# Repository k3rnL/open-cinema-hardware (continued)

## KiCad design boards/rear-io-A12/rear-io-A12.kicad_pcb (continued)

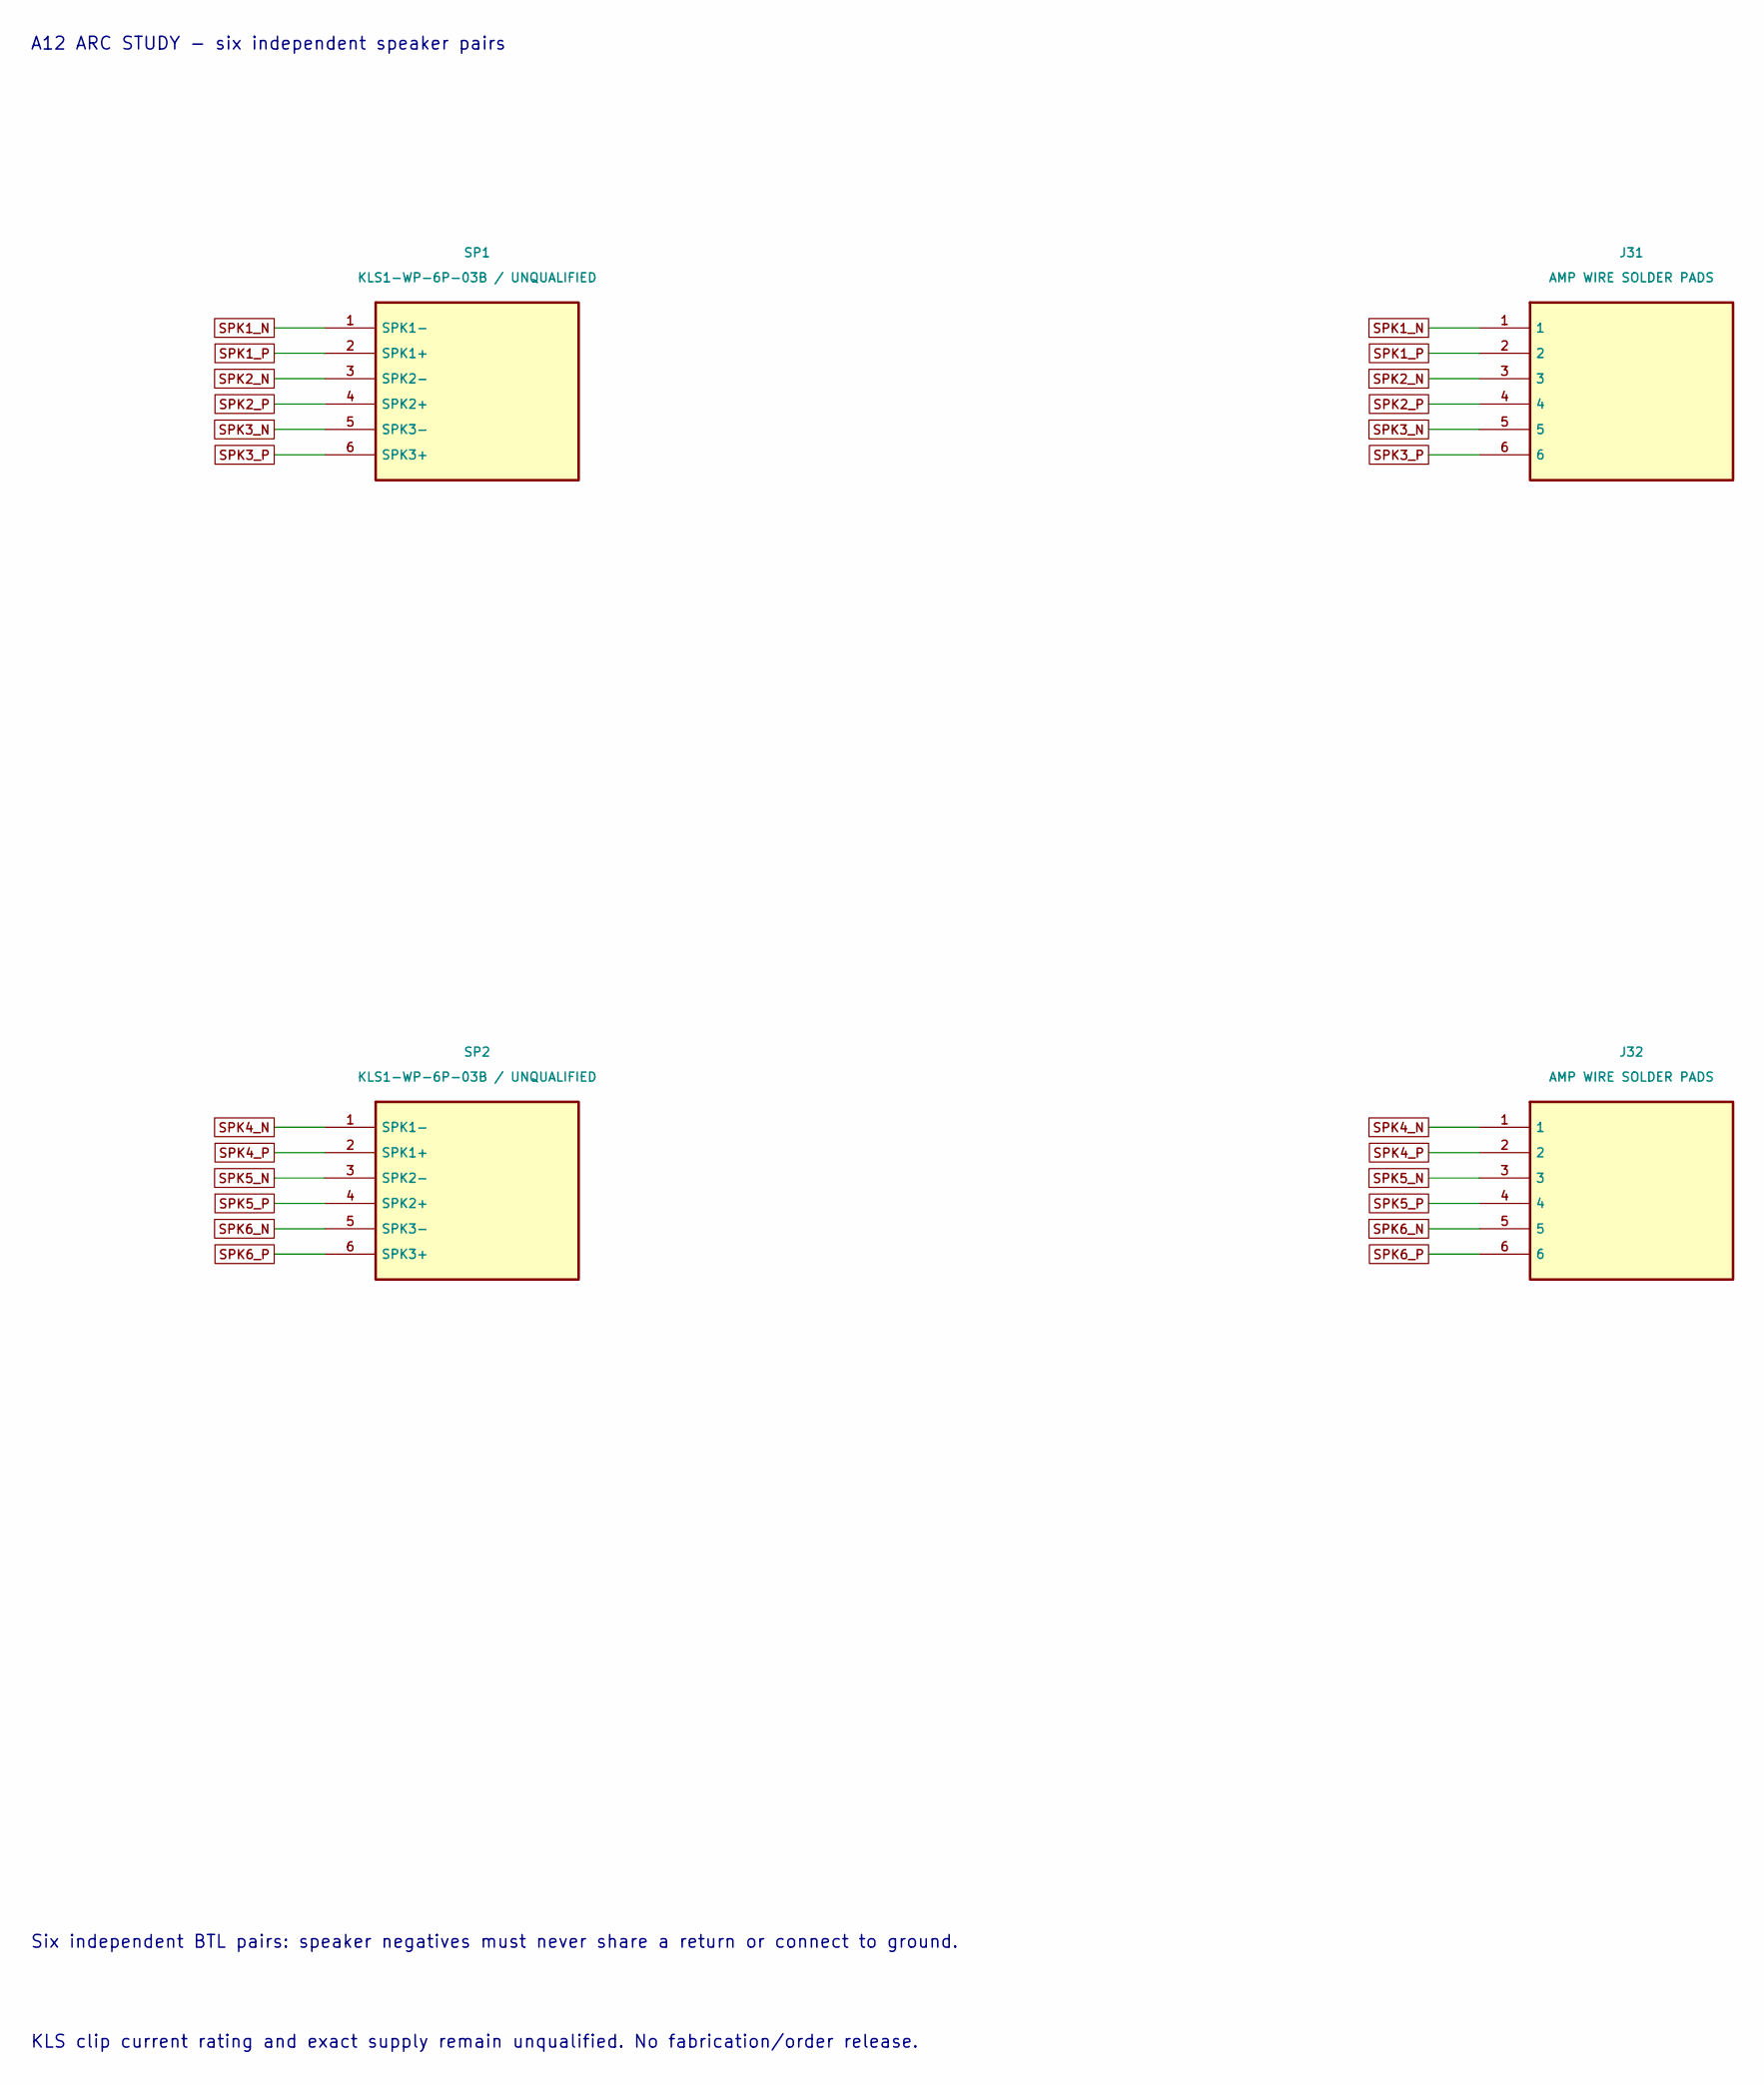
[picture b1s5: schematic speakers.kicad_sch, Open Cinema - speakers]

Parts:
J31, J32: AMP WIRE SOLDER PADS; SolderWire-1sqmm_1x06_P5.4mm_D1.4mm_OD2.7mm; MPN PCB_SOLDER_PADS_1SQMM
SP1, SP2: KLS1-WP-6P-03B / UNQUALIFIED; KLS1_WP_6P_03B_Horizontal_A8; MPN L-KLS1-WP-6P-03B-B/R

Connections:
SPK1_N: J31.1, SP1.1 (SPK1-)
SPK1_P: J31.2, SP1.2 (SPK1+)
SPK2_N: J31.3, SP1.3 (SPK2-)
SPK2_P: J31.4, SP1.4 (SPK2+)
SPK3_N: J31.5, SP1.5 (SPK3-)
SPK3_P: J31.6, SP1.6 (SPK3+)
SPK4_N: J32.1, SP2.1 (SPK1-)
SPK4_P: J32.2, SP2.2 (SPK1+)
SPK5_N: J32.3, SP2.3 (SPK2-)
SPK5_P: J32.4, SP2.4 (SPK2+)
SPK6_N: J32.5, SP2.5 (SPK3-)
SPK6_P: J32.6, SP2.6 (SPK3+)

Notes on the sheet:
A12 ARC STUDY - six independent speaker pairs
Six independent BTL pairs: speaker negatives must never share a return or connect to ground.
KLS clip current rating and exact supply remain unqualified. No fabrication/order release.

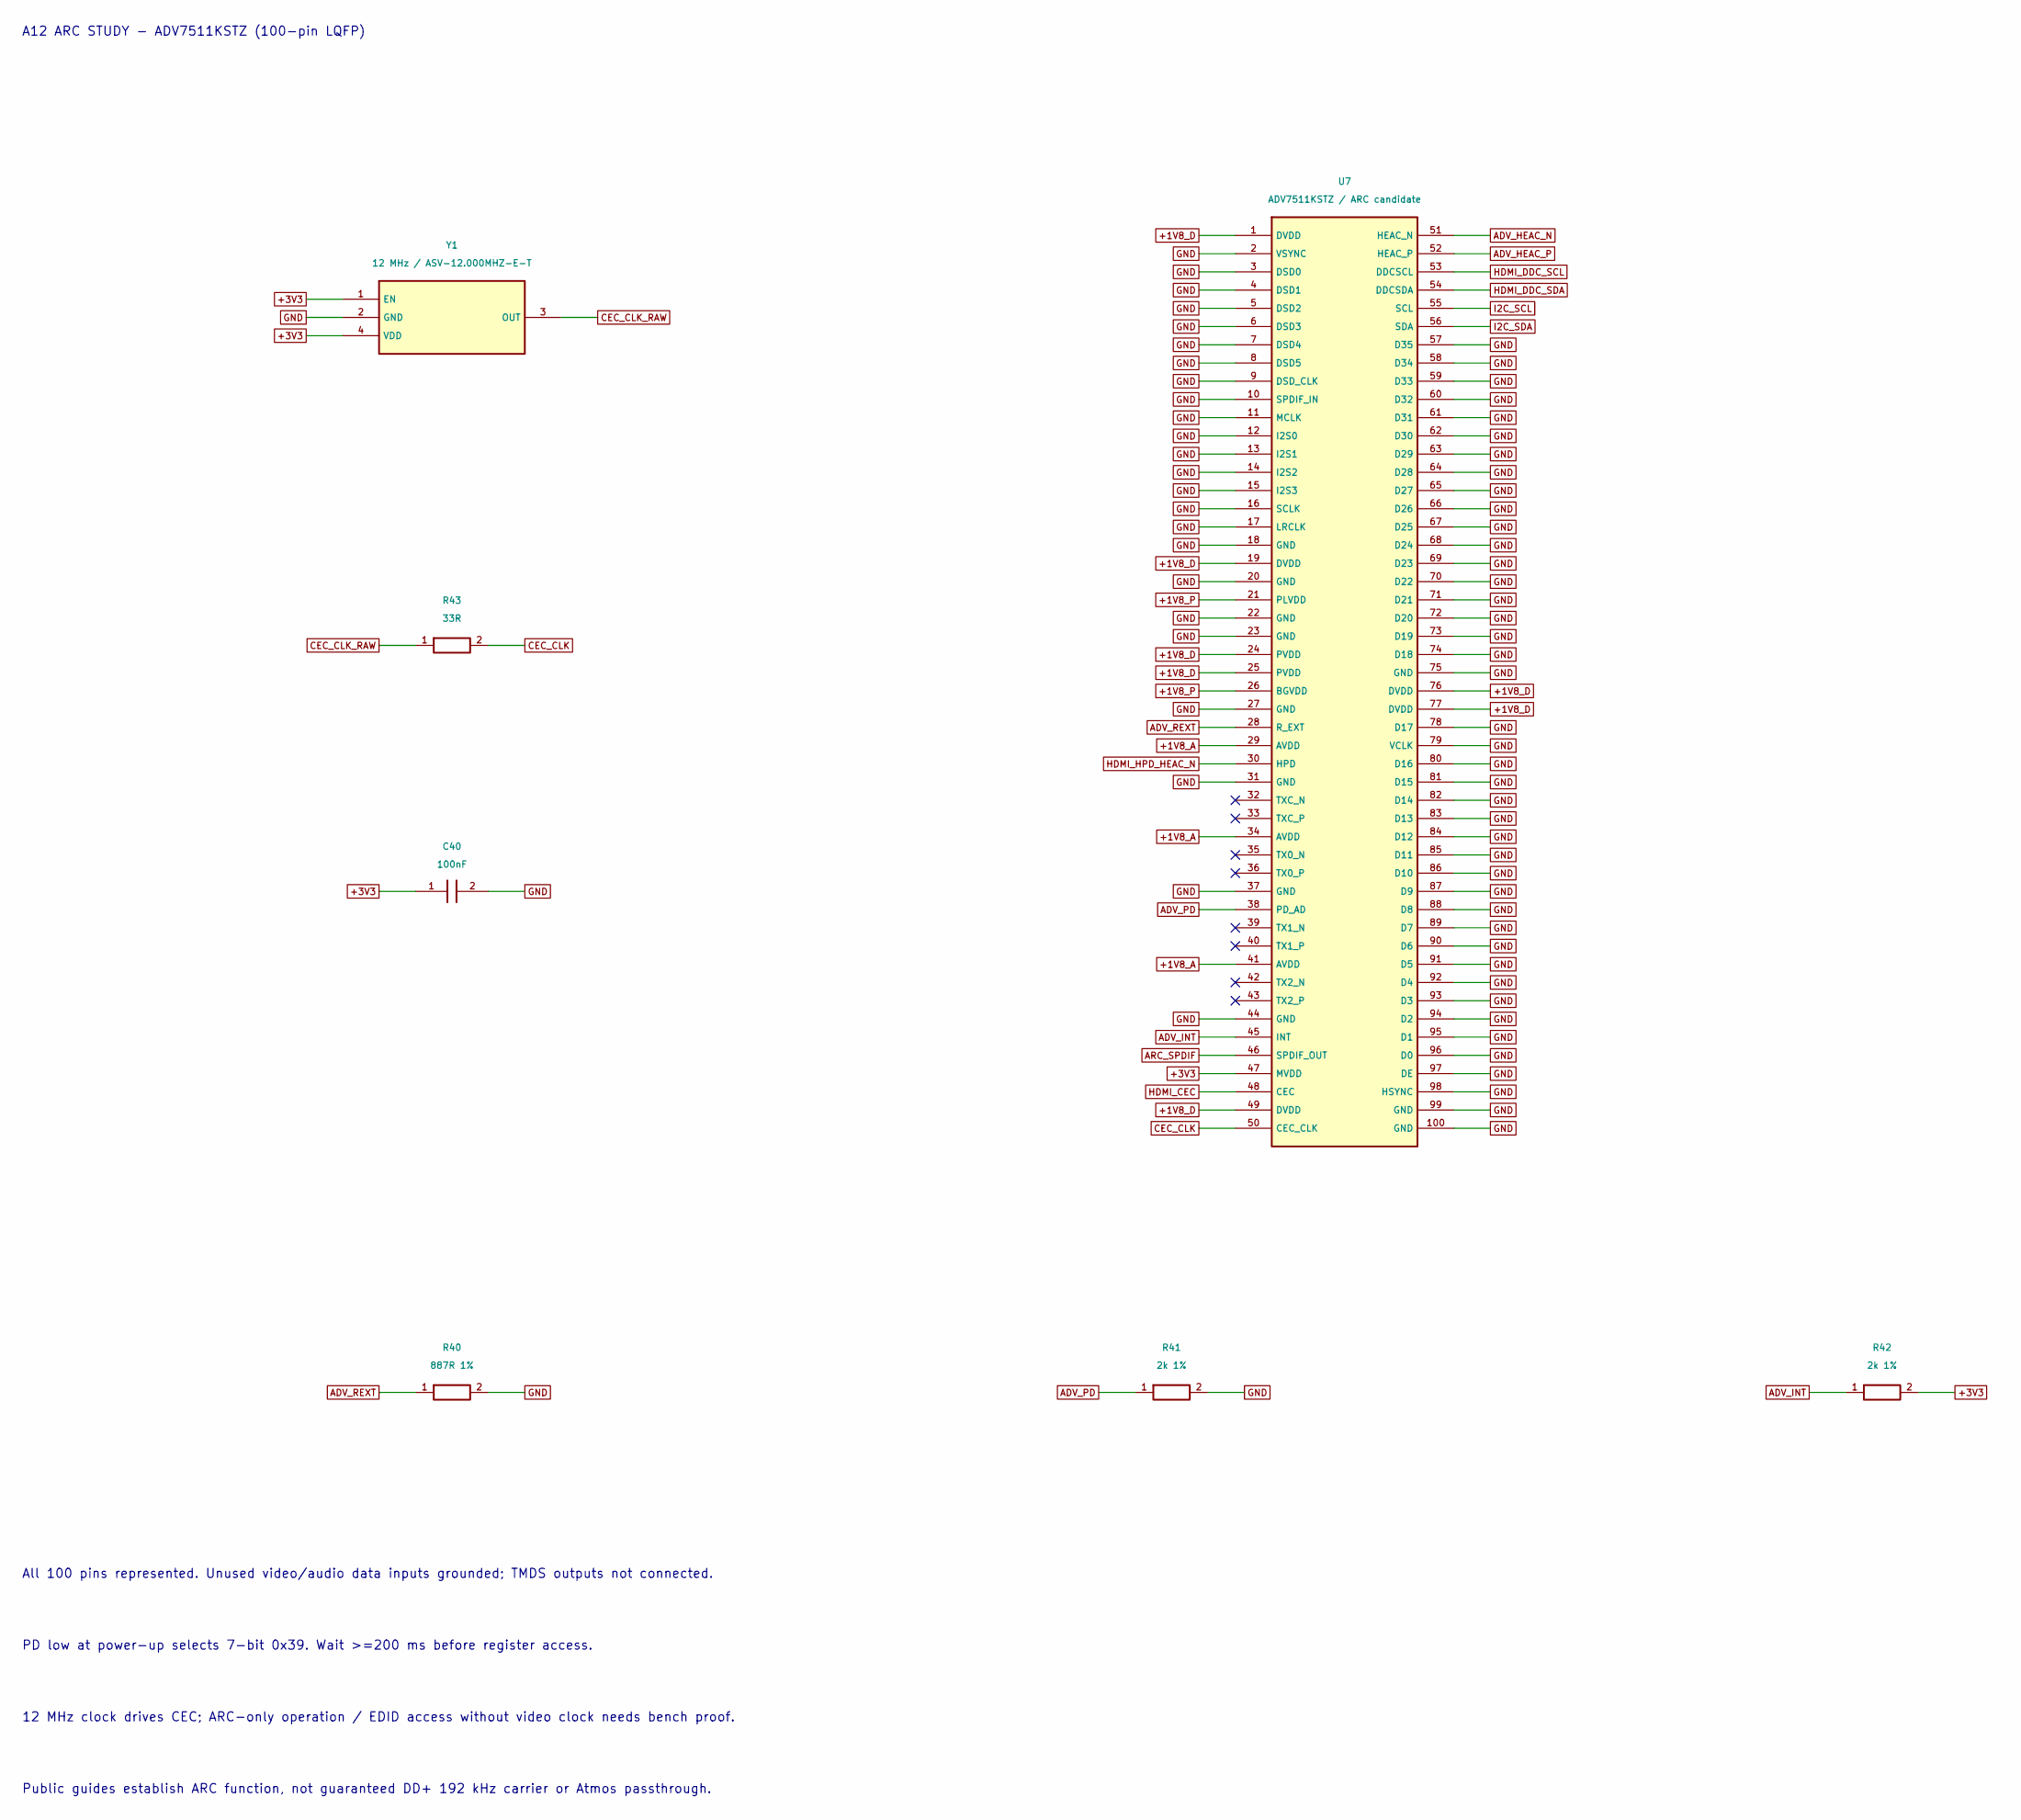
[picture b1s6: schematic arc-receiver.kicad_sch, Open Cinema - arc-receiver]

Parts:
C40: 100nF; C_0603_1608Metric; MPN CL10B104KB8NNNC
R40: 887R 1%; R_0603_1608Metric; MPN RC0603FR-07887RL
R41, R42: 2k 1%; R_0603_1608Metric; MPN RC0603FR-072KL
R43: 33R; R_0603_1608Metric; MPN RC0603FR-0733RL
U7: ADV7511KSTZ / ARC candidate; LQFP-100_14x14mm_P0.5mm; MPN ADV7511KSTZ
Y1: 12 MHz / ASV-12.000MHZ-E-T; Oscillator_SMD_Abracon_ASV-4Pin_7.0x5.1mm; MPN ASV-12.000MHZ-E-T

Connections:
+1V8_A: U7.29 (AVDD), U7.34 (AVDD), U7.41 (AVDD); also elsewhere on the board
+1V8_D: U7.1 (DVDD), U7.19 (DVDD), U7.24 (PVDD), U7.25 (PVDD), U7.49 (DVDD), U7.76 (DVDD), U7.77 (DVDD); also elsewhere on the board
+1V8_P: U7.21 (PLVDD), U7.26 (BGVDD); also elsewhere on the board
+3V3: C40.1, R42.2, U7.47 (MVDD), Y1.1 (EN), Y1.4 (VDD); also elsewhere on the board
ADV_HEAC_N: U7.51 (HEAC_N); also elsewhere on the board
ADV_HEAC_P: U7.52 (HEAC_P); also elsewhere on the board
ADV_INT: R42.1, U7.45 (INT); also elsewhere on the board
ADV_PD: R41.1, U7.38 (PD_AD)
ADV_REXT: R40.1, U7.28 (R_EXT)
ARC_SPDIF: U7.46 (SPDIF_OUT); also elsewhere on the board
CEC_CLK: R43.2, U7.50 (CEC_CLK)
CEC_CLK_RAW: R43.1, Y1.3 (OUT)
GND: C40.2, R40.2, R41.2, U7.2 (VSYNC), U7.3 (DSD0), U7.4 (DSD1), U7.5 (DSD2), U7.6 (DSD3), U7.7 (DSD4), U7.8 (DSD5), U7.9 (DSD_CLK), U7.10 (SPDIF_IN), U7.11 (MCLK), U7.12 (I2S0), U7.13 (I2S1), U7.14 (I2S2), U7.15 (I2S3), U7.16 (SCLK), U7.17 (LRCLK), U7.18 (GND), U7.20 (GND), U7.22 (GND), U7.23 (GND), U7.27 (GND), U7.31 (GND), U7.37 (GND), U7.44 (GND), U7.57 (D35), U7.58 (D34), U7.59 (D33), U7.60 (D32), U7.61 (D31), U7.62 (D30), U7.63 (D29), U7.64 (D28), U7.65 (D27), U7.66 (D26), U7.67 (D25), U7.68 (D24), U7.69 (D23), U7.70 (D22), U7.71 (D21), U7.72 (D20), U7.73 (D19), U7.74 (D18), U7.75 (GND), U7.78 (D17), U7.79 (VCLK), U7.80 (D16), U7.81 (D15), U7.82 (D14), U7.83 (D13), U7.84 (D12), U7.85 (D11), U7.86 (D10), U7.87 (D9), U7.88 (D8), U7.89 (D7), U7.90 (D6), U7.91 (D5), U7.92 (D4), U7.93 (D3), U7.94 (D2), U7.95 (D1), U7.96 (D0), U7.97 (DE), U7.98 (HSYNC), U7.99 (GND), U7.100 (GND), Y1.2 (GND); also elsewhere on the board
HDMI_CEC: U7.48 (CEC); also elsewhere on the board
HDMI_DDC_SCL: U7.53 (DDCSCL); also elsewhere on the board
HDMI_DDC_SDA: U7.54 (DDCSDA); also elsewhere on the board
HDMI_HPD_HEAC_N: U7.30 (HPD); also elsewhere on the board
I2C_SCL: U7.55 (SCL); also elsewhere on the board
I2C_SDA: U7.56 (SDA); also elsewhere on the board

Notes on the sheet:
A12 ARC STUDY - ADV7511KSTZ (100-pin LQFP)
All 100 pins represented. Unused video/audio data inputs grounded; TMDS outputs not connected.
PD low at power-up selects 7-bit 0x39. Wait >=200 ms before register access.
12 MHz clock drives CEC; ARC-only operation / EDID access without video clock needs bench proof.
Public guides establish ARC function, not guaranteed DD+ 192 kHz carrier or Atmos passthrough.

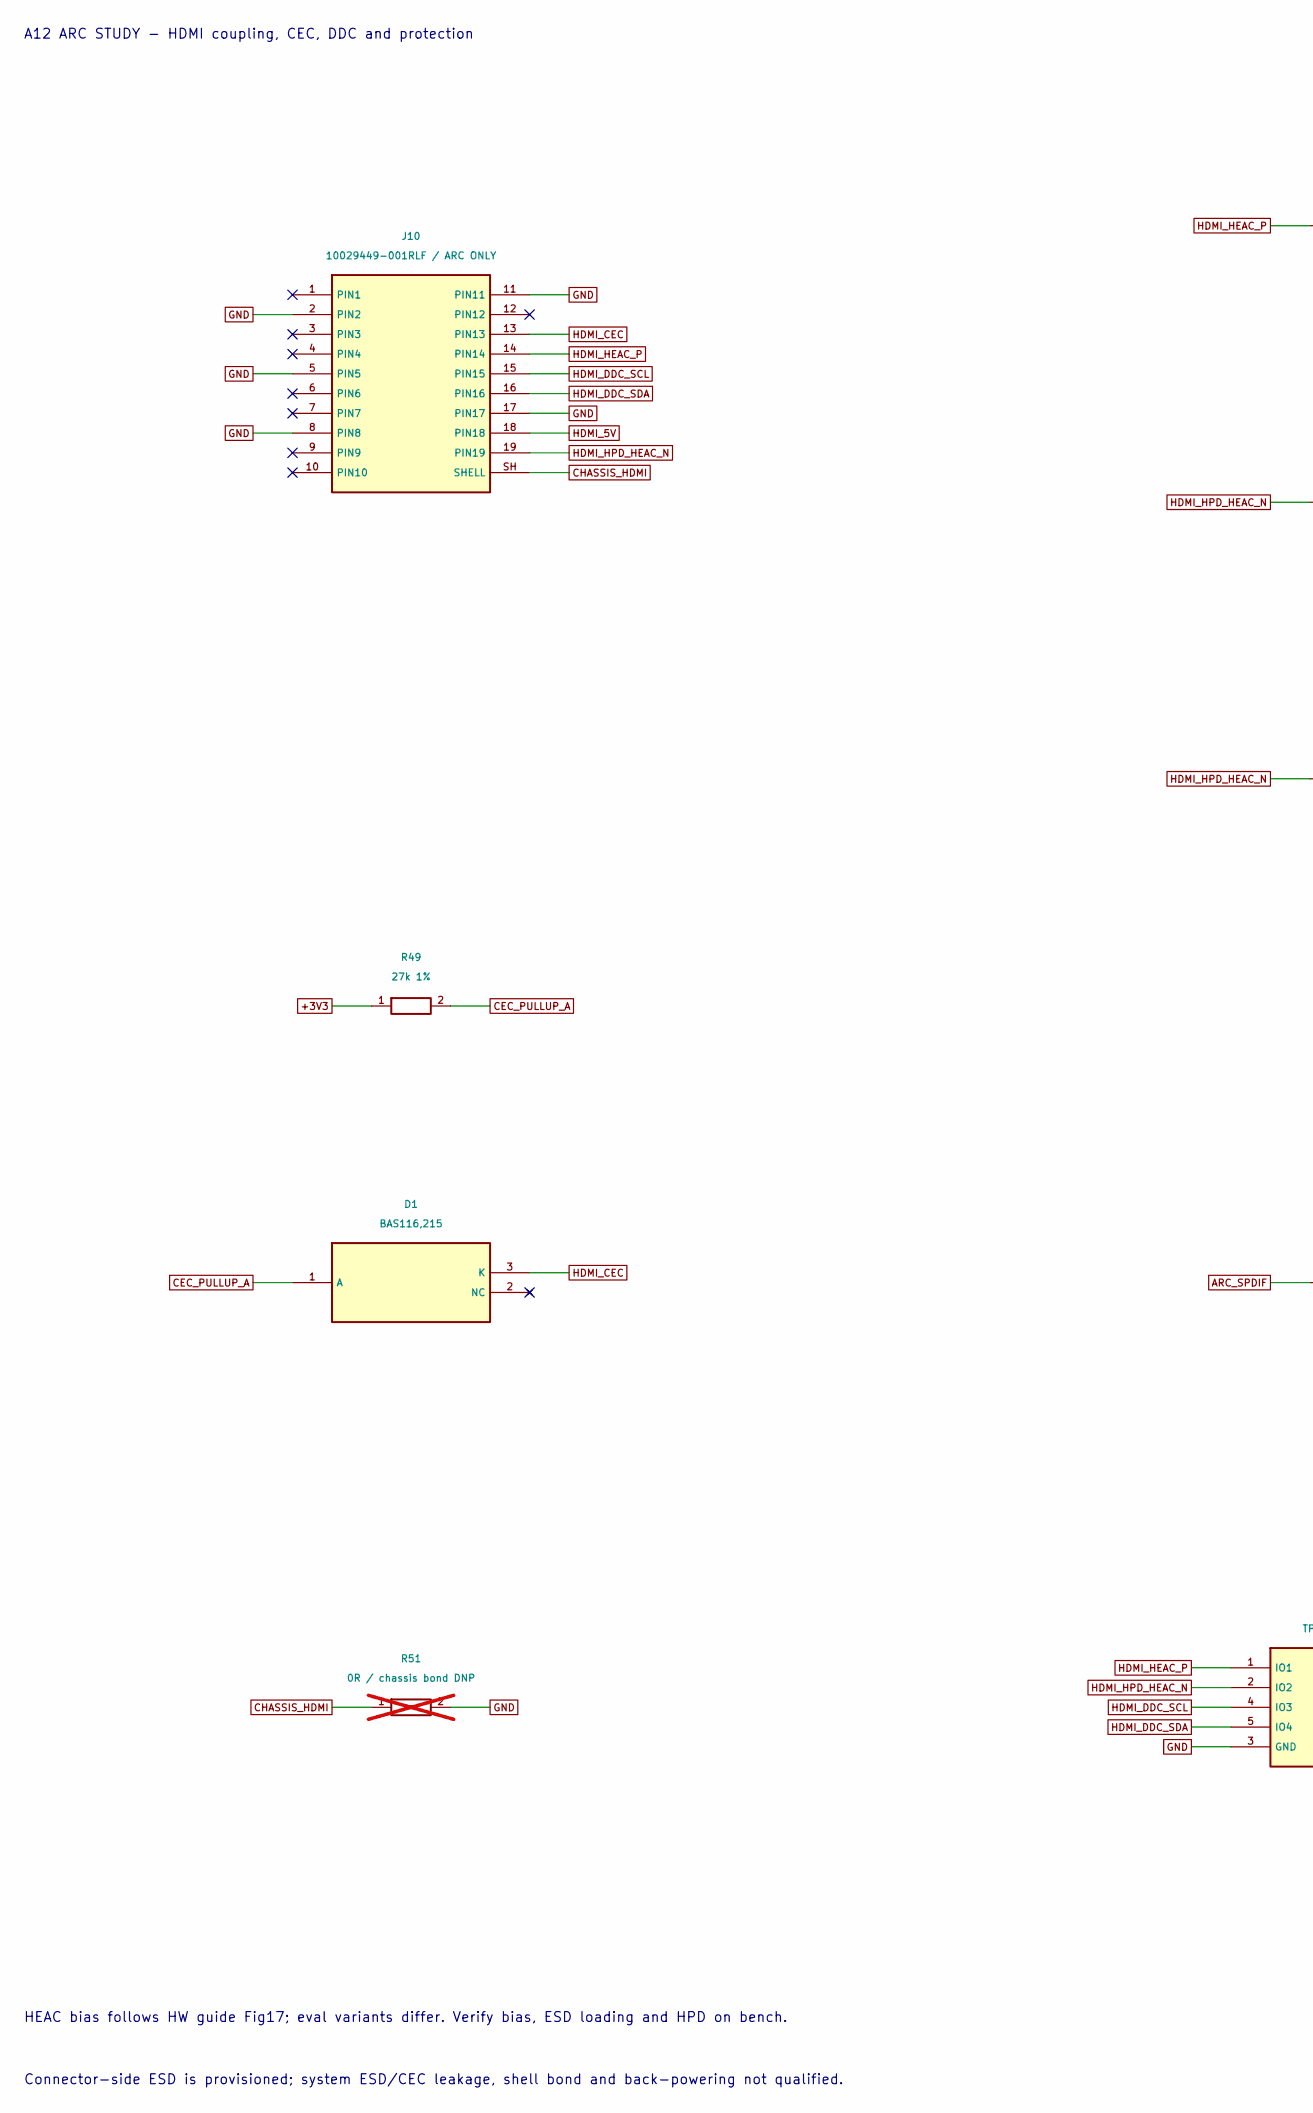
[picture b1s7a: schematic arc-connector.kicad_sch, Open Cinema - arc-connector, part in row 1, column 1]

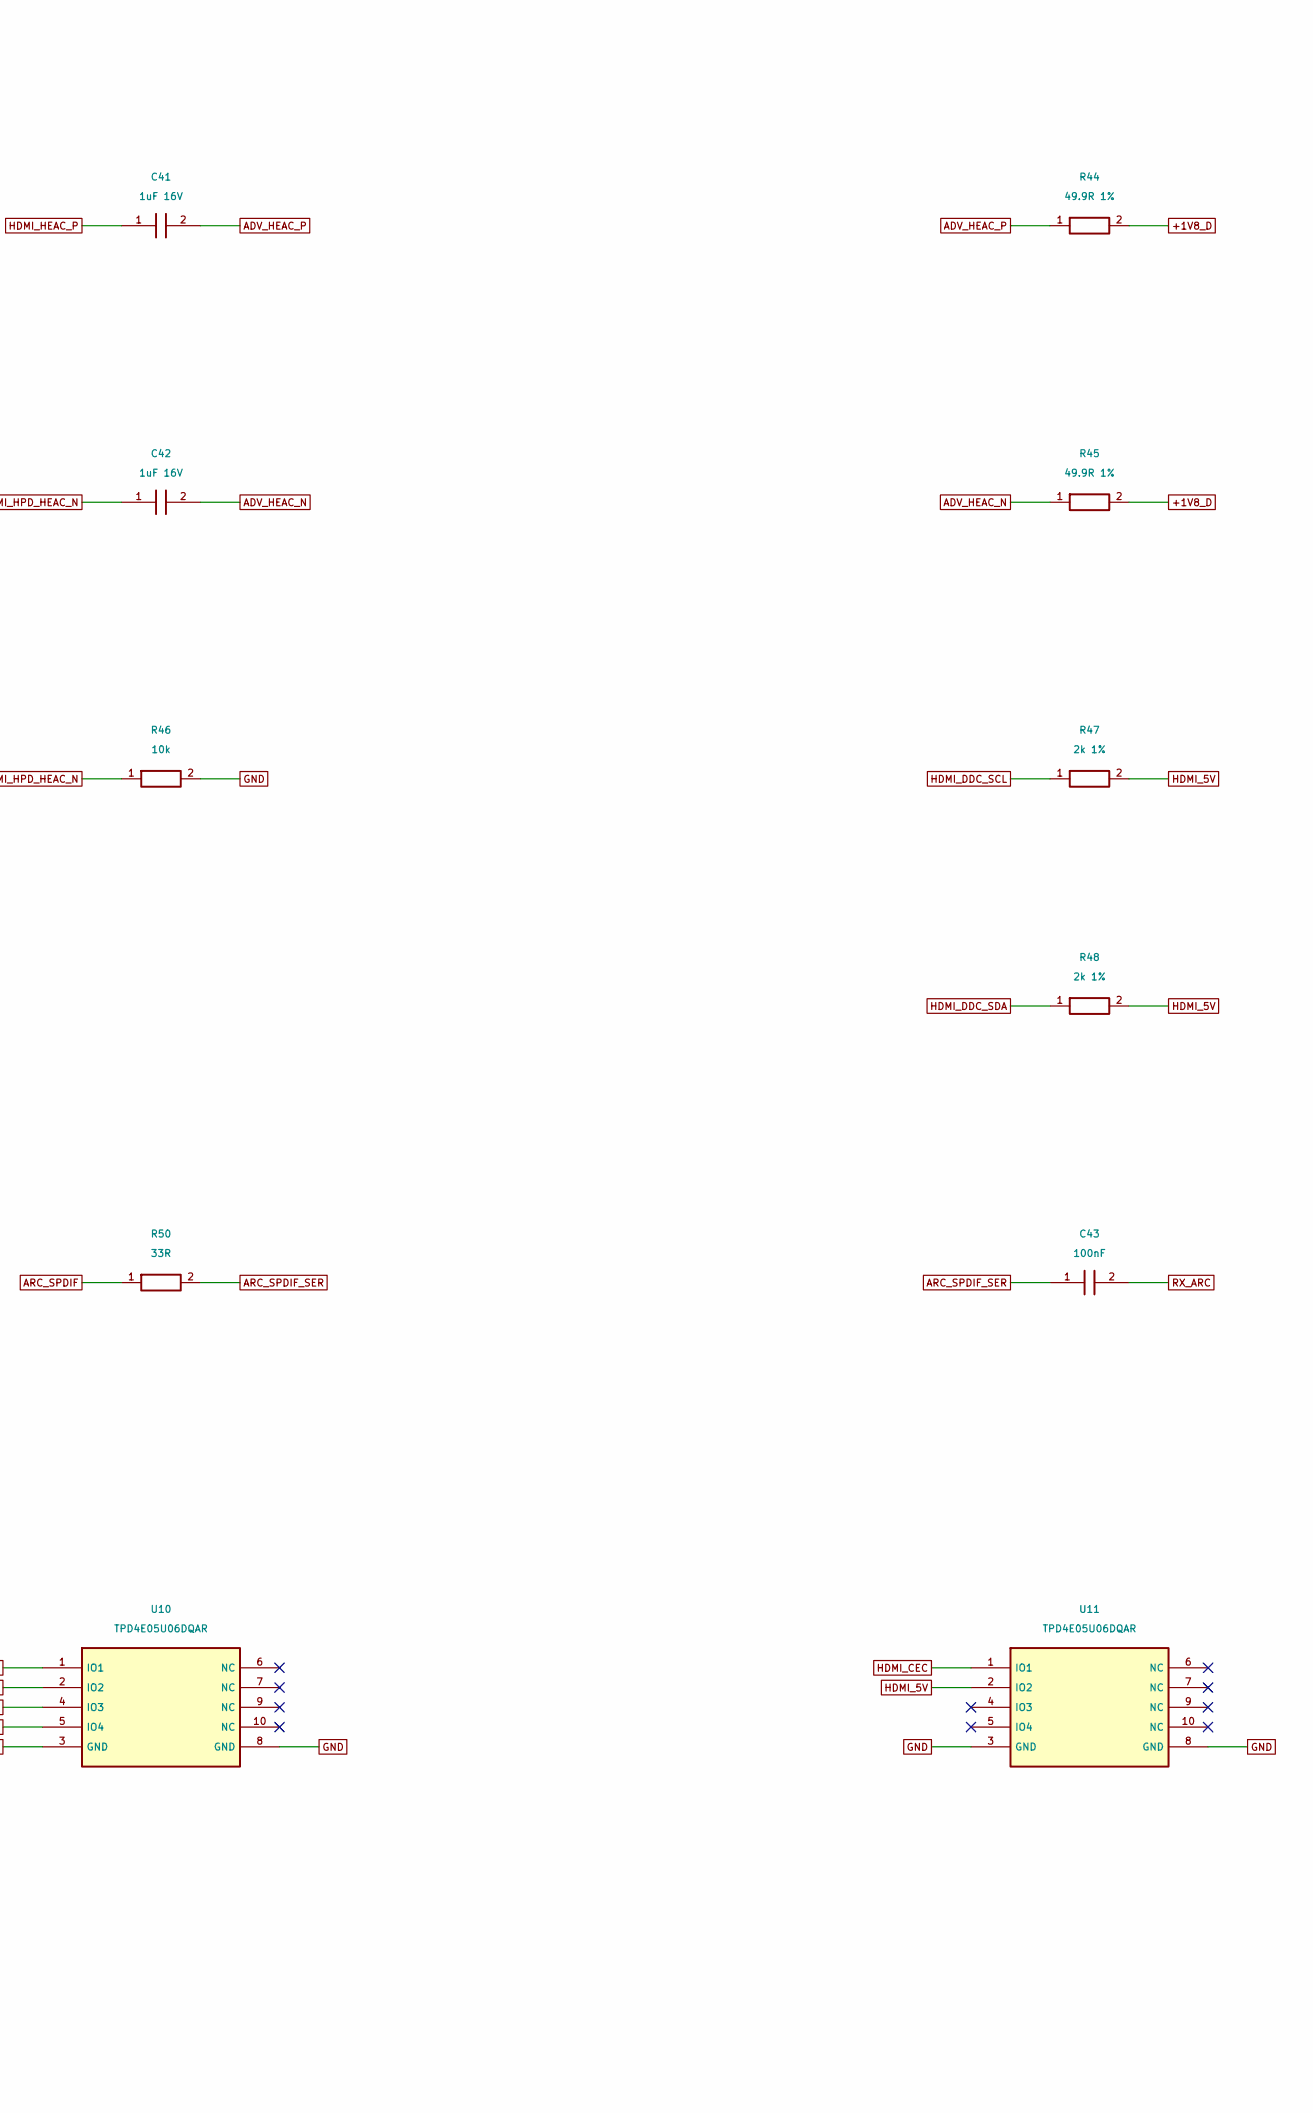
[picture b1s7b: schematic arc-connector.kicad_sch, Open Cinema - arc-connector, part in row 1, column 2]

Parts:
C41, C42: 1uF 16V; C_0603_1608Metric; MPN CL10B105KO8NNNC
C43: 100nF; C_0603_1608Metric; MPN CL10B104KB8NNNC
D1: BAS116,215; SOT-23; MPN BAS116,215
J10: 10029449-001RLF / ARC ONLY; HDMI_A_Amphenol_10029449-x01xLF_Horizontal; MPN 10029449-001RLF
R44, R45: 49.9R 1%; R_0603_1608Metric; MPN RC0603FR-0749R9L
R46: 10k; R_0603_1608Metric; MPN RC0603FR-0710KL
R47, R48: 2k 1%; R_0603_1608Metric; MPN RC0603FR-072KL
R49: 27k 1%; R_0603_1608Metric; MPN RC0603FR-0727KL
R50: 33R; R_0603_1608Metric; MPN RC0603FR-0733RL
R51: 0R / chassis bond DNP; R_0603_1608Metric; MPN RC0603JR-070RL; not fitted
U10, U11: TPD4E05U06DQAR; USON-10_2.5x1.0mm_P0.5mm; MPN TPD4E05U06DQAR

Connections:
+1V8_D: R44.2, R45.2; also elsewhere on the board
+3V3: R49.1; also elsewhere on the board
ADV_HEAC_N: C42.2, R45.1; also elsewhere on the board
ADV_HEAC_P: C41.2, R44.1; also elsewhere on the board
ARC_SPDIF: R50.1; also elsewhere on the board
ARC_SPDIF_SER: C43.1, R50.2
CEC_PULLUP_A: D1.1 (A), R49.2
CHASSIS_HDMI: J10.SH (SHELL), R51.1
GND: J10.2 (PIN2), J10.5 (PIN5), J10.8 (PIN8), J10.11 (PIN11), J10.17 (PIN17), R46.2, R51.2, U10.3 (GND), U10.8 (GND), U11.3 (GND), U11.8 (GND); also elsewhere on the board
HDMI_5V: J10.18 (PIN18), R47.2, R48.2, U11.2 (IO2); also elsewhere on the board
HDMI_CEC: D1.3 (K), J10.13 (PIN13), U11.1 (IO1); also elsewhere on the board
HDMI_DDC_SCL: J10.15 (PIN15), R47.1, U10.4 (IO3); also elsewhere on the board
HDMI_DDC_SDA: J10.16 (PIN16), R48.1, U10.5 (IO4); also elsewhere on the board
HDMI_HEAC_P: C41.1, J10.14 (PIN14), U10.1 (IO1)
HDMI_HPD_HEAC_N: C42.1, J10.19 (PIN19), R46.1, U10.2 (IO2); also elsewhere on the board
RX_ARC: C43.2; also elsewhere on the board

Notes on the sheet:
A12 ARC STUDY - HDMI coupling, CEC, DDC and protection
HEAC bias follows HW guide Fig17; eval variants differ. Verify bias, ESD loading and HPD on bench.
Connector-side ESD is provisioned; system ESD/CEC leakage, shell bond and back-powering not qualified.

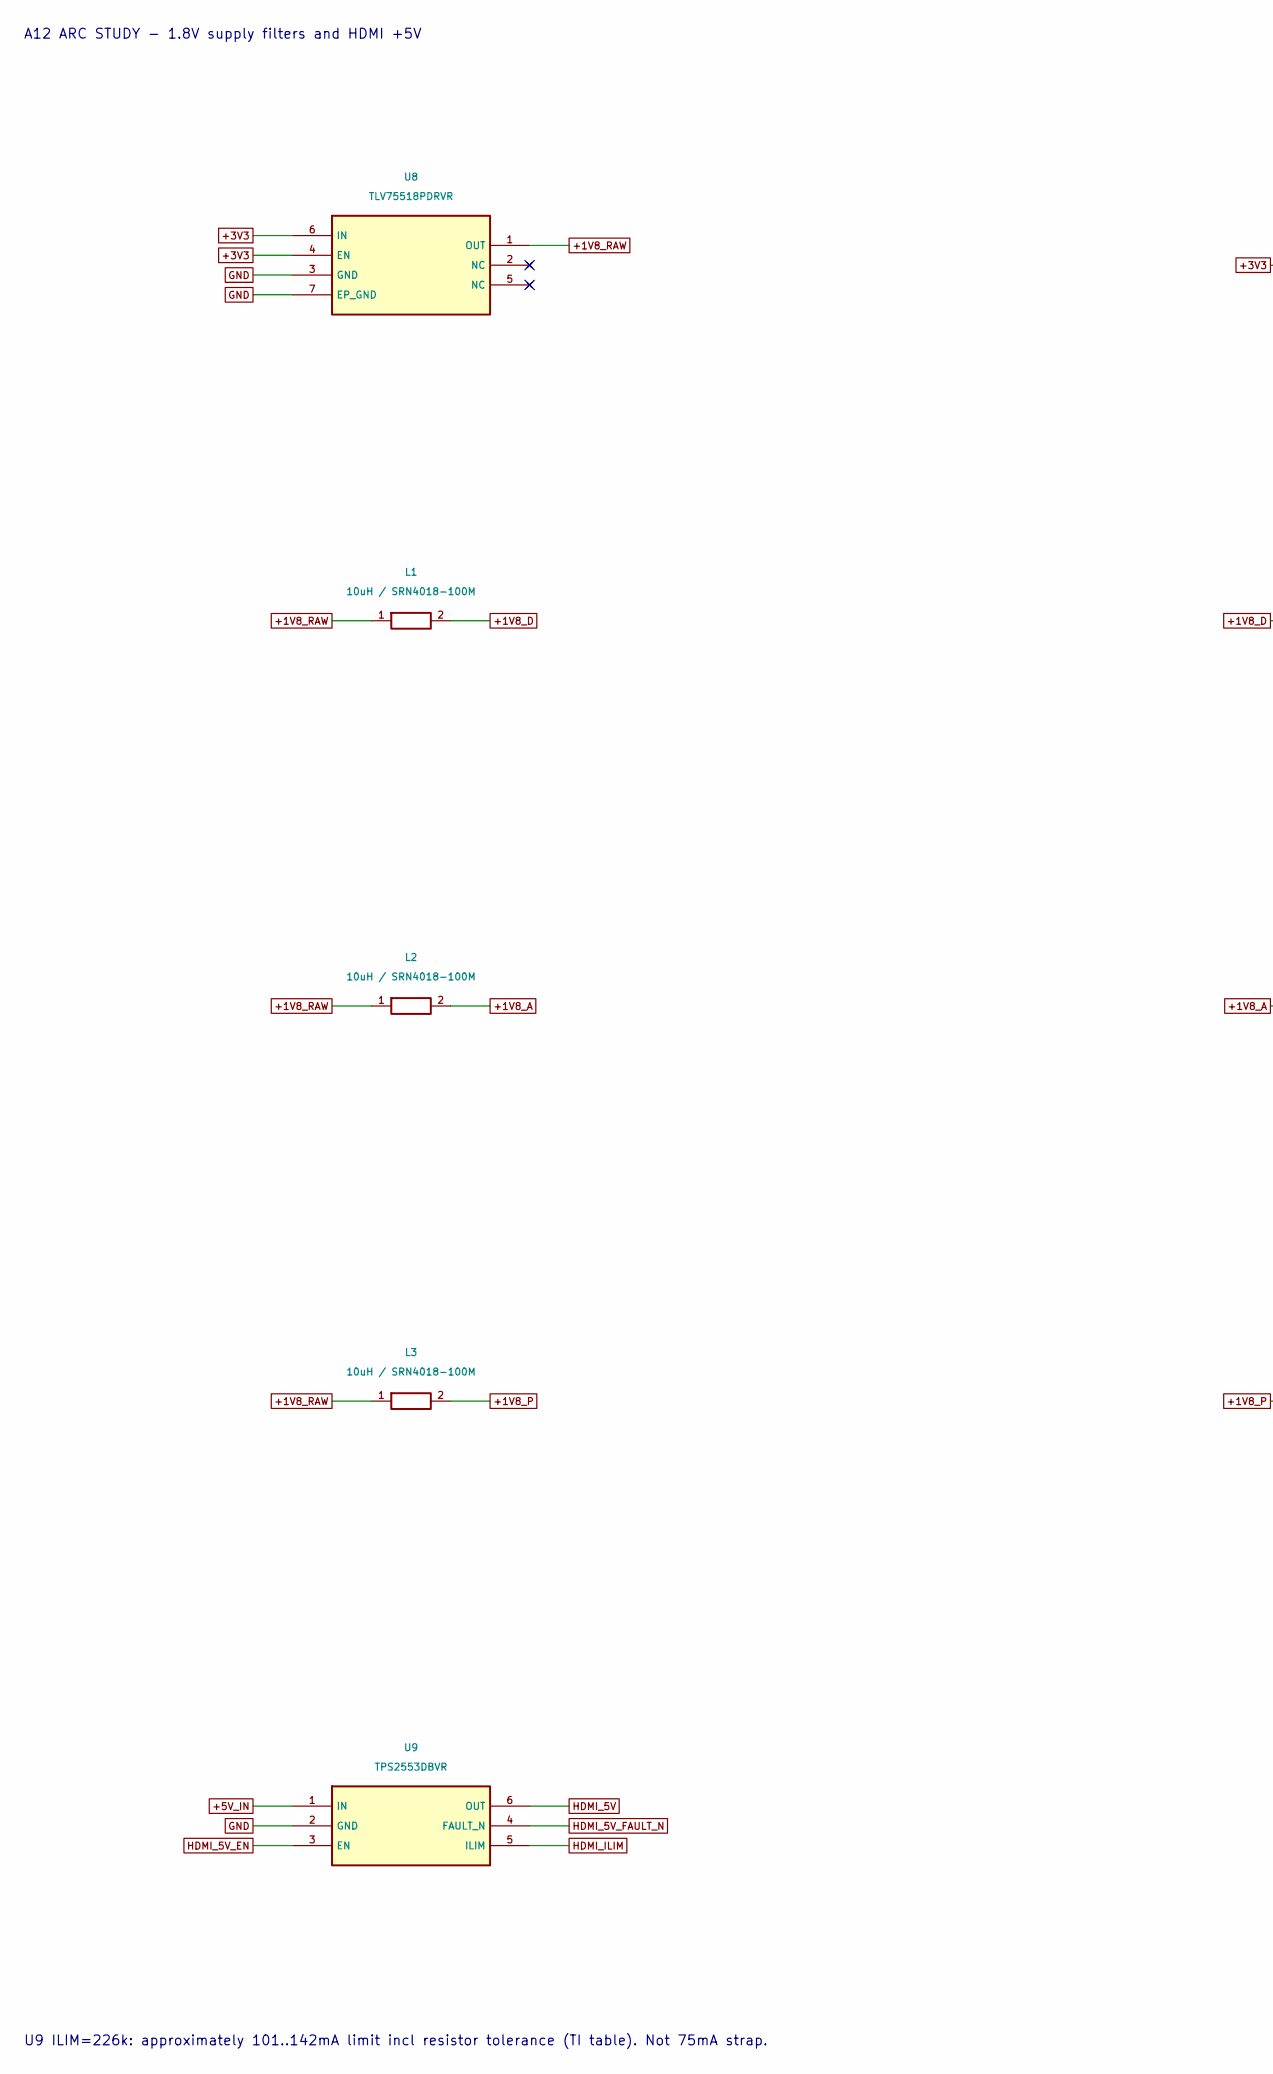
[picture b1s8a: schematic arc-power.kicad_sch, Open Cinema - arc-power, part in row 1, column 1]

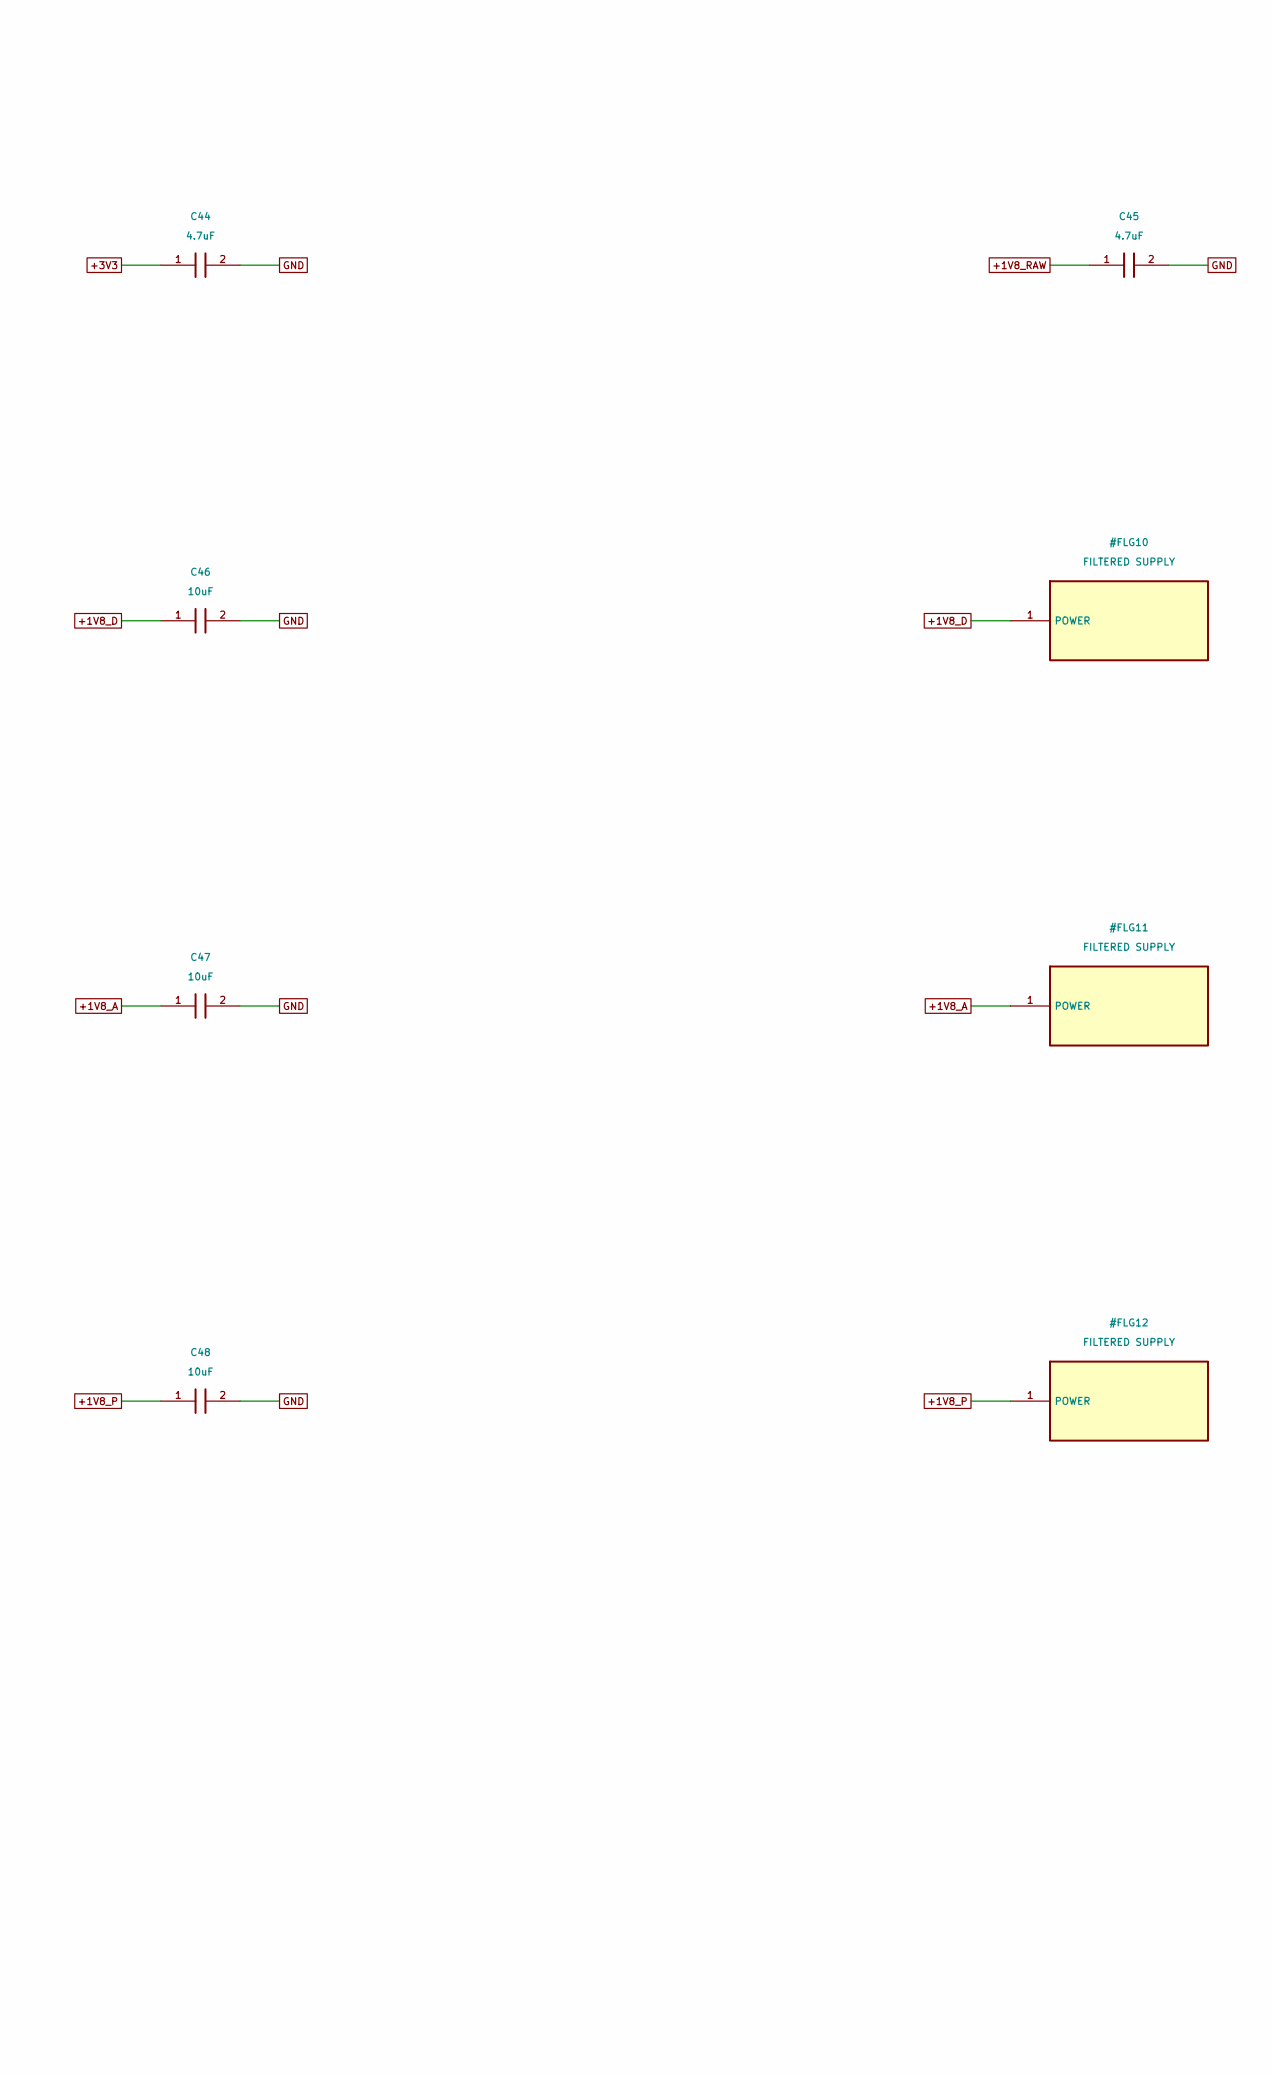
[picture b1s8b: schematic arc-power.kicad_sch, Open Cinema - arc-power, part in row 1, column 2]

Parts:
C44, C45: 4.7uF; C_0603_1608Metric; MPN CL10A475KO8NNNC
C46, C47, C48: 10uF; C_0603_1608Metric; MPN CL10A106KP8NNNC
L1, L2, L3: 10uH / SRN4018-100M; L_Bourns-SRN4018; MPN SRN4018-100M
U8: TLV75518PDRVR; WSON-6-1EP_2x2mm_P0.65mm_EP1x1.6mm; MPN TLV75518PDRVR
U9: TPS2553DBVR; SOT-23-6; MPN TPS2553DBVR

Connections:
+1V8_A: C47.1, L2.2; also elsewhere on the board
+1V8_D: C46.1, L1.2; also elsewhere on the board
+1V8_P: C48.1, L3.2; also elsewhere on the board
+1V8_RAW: C45.1, L1.1, L2.1, L3.1, U8.1 (OUT)
+3V3: C44.1, U8.4 (EN), U8.6 (IN); also elsewhere on the board
+5V_IN: U9.1 (IN); also elsewhere on the board
GND: C44.2, C45.2, C46.2, C47.2, C48.2, U8.3 (GND), U8.7 (EP_GND), U9.2 (GND); also elsewhere on the board
HDMI_5V: U9.6 (OUT); also elsewhere on the board
HDMI_5V_EN: U9.3 (EN); also elsewhere on the board
HDMI_5V_FAULT_N: U9.4 (FAULT_N); also elsewhere on the board
HDMI_ILIM: U9.5 (ILIM); also elsewhere on the board

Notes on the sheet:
A12 ARC STUDY - 1.8V supply filters and HDMI +5V
U9 ILIM=226k: approximately 101..142mA limit incl resistor tolerance (TI table). Not 75mA strap.
